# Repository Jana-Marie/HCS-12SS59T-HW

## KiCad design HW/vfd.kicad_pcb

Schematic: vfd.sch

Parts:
BT1: Battery_Cell; BatteryHolder_Keystone_1042_1x18650
C1, C3, C9, C10, C12, C14, C17, C18, C19, C21: 1u; C_0805_2012Metric
C2, C4, C6, C8, C11, C13, C15, C16, C20, C22: 100n; C_0603_1608Metric
C5: 82p; C_0603_1608Metric
C7: TBD; C_0603_1608Metric
D1, D2: D_Schottky; D_SMA
D3: led; LED_0603_1608Metric
L1, L2, L3: 15u; L_Taiyo-Yuden_MD-4040
Q1, Q3, Q5, Q6: 2N7002; SOT-23
Q2, Q4: Si2319CDS; SOT-23
R1: 470; R_0603_1608Metric
R2: 8k2; R_0603_1608Metric
R3, R4, R5, R6, R7, R10: 47; R_0603_1608Metric
R8, R9, R18: 10k; R_0603_1608Metric
R11: TBD; R_0603_1608Metric
R12: 25k; R_0603_1608Metric
R13, R14, R16: 1k; R_0603_1608Metric
R15: 3k; R_0603_1608Metric
R17: 1k5; R_0603_1608Metric
SW1: SW_DIP_x01
T1: Transformer_1P_1S; SRF0703
U1: HCS-12SS59T
U2, U3: MCP1663; SOT-23-5
U4: LM3670MF; SOT-23-5
U5: TP4056; SO-8_5.3x6.2mm_P1.27mm
U6: ESP32-wroom-32; ESP-wroom-32

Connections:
+3V3: C15.1, C17.1, C21.1, C22.1, L3.2, Q2.2 (S), Q4.2 (S), R18.1, U4.4 (FB), U6.2
+5V: C2.1, C16.1, C18.1, D2.1, R2.1, R8.1, R9.1, U1.5
+36V: C3.1, C8.1, C9.1, D1.1, R1.2
CLK: U1.11
CS: U1.10
DIN: U1.12
EN: C20.1, R18.2, U6.3
F+: T1.4, U1.44, U1.45
F-: T1.3, U1.1, U1.2
GND: BT1.2, C1.2, C2.2, C3.2, C4.2, C5.2, C6.2, C7.2, C8.2, C9.2, C10.2, C11.2, C12.2, C13.2, C14.2, C15.2, C16.2, C17.2, C18.2, C19.2, C20.2, C21.2, C22.2, Q1.2 (S), Q3.2 (S), Q5.2 (S), Q6.2 (S), R13.1, R16.1, R17.2, U1.7, U2.2, U3.2, U4.2 (GND), U5.1, U5.3, U6.1, U6.15, U6.38
GPIO15: R7.2
GPIO16: R10.1
unnamed: C4.1, R1.1, U1.6
unnamed: C5.1, R2.2, U1.8
unnamed: C7.1, R11.1, U2.4
unnamed: D1.2, L1.2, R12.2, U2.1
unnamed: D2.2, L2.2, R15.2, U3.1
unnamed: D3.1, R14.1
unnamed: L3.1, U4.5 (SW)
unnamed: Q1.1 (G), R7.1
unnamed: Q1.3 (D), R3.2, R4.2, R8.2
unnamed: Q2.1 (G), R3.1
unnamed: Q2.3 (D), Q3.3 (D), T1.2
unnamed: Q3.1 (G), R4.1
unnamed: Q4.1 (G), R5.2
unnamed: Q4.3 (D), Q5.3 (D), T1.1
unnamed: Q5.1 (G), R6.2
unnamed: Q6.1 (G), R10.2
unnamed: Q6.3 (D), R5.1, R6.1, R9.2
unnamed: R12.1, R13.2, U2.3
unnamed: R14.2, U5.7
unnamed: R15.1, R16.2, U3.3
unnamed: R17.1, U5.2
RST: U1.9
VBAT: BT1.1, C19.1, U5.5
VBAT_SW: C1.1, C6.1, C10.1, C11.1, C12.1, C13.1, L1.1, L2.1, R11.2, U2.5, U3.4, U3.5, U4.1 (Vin), U4.3 (EN)
VUSB: C14.1, D3.2, U5.4, U5.8

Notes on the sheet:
Todo: ESP Unterspannungsschutz USB-seriell Otter

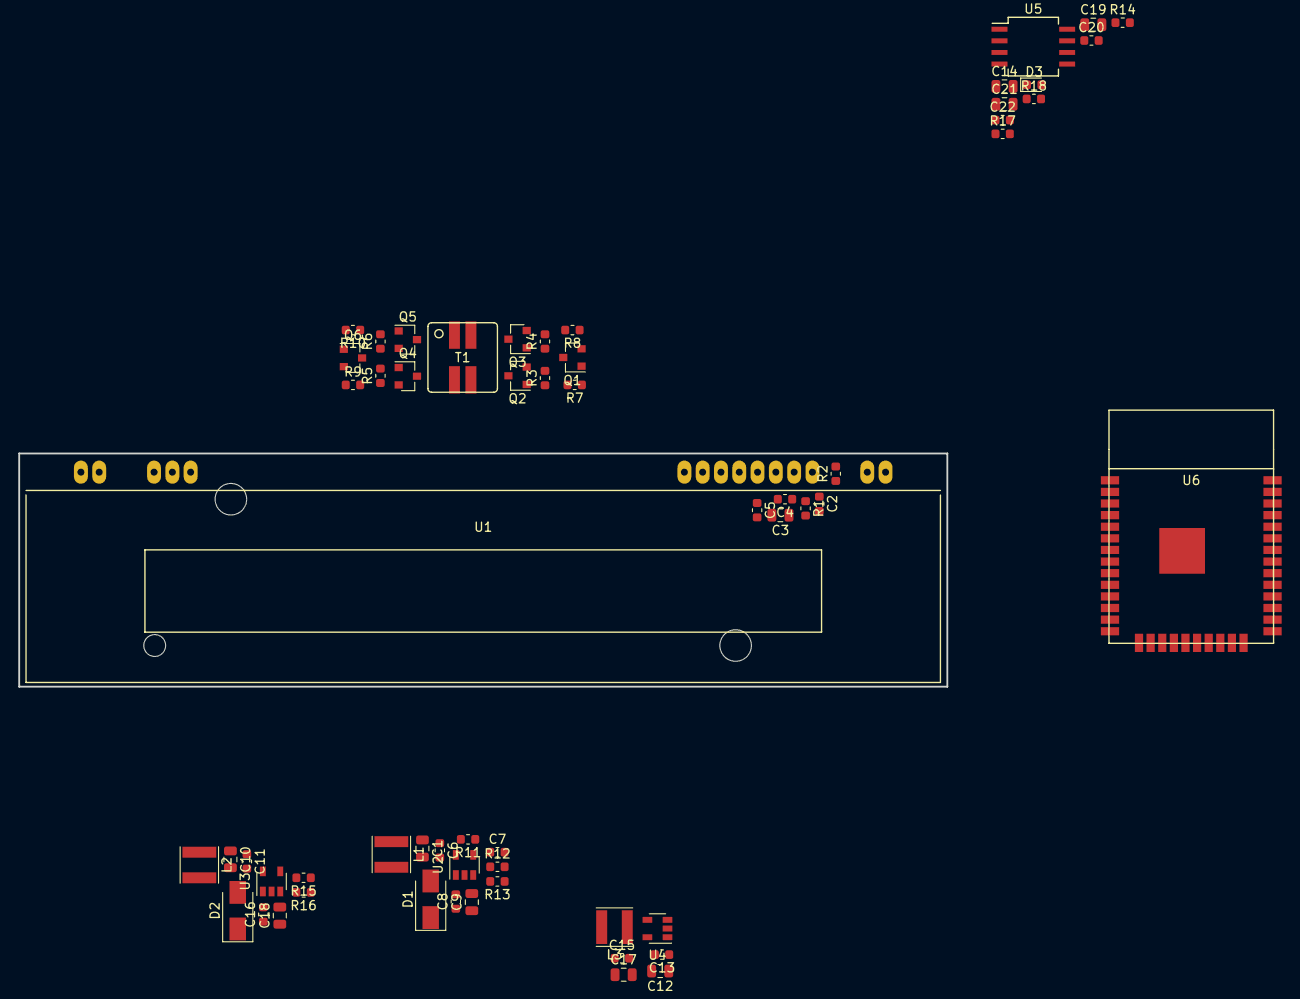
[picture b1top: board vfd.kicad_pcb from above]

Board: 2 copper layers, 101.5 x 25.5 mm, 60 parts (1 on the bottom side), 31 nets, no tracks yet.

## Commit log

2018-09-24 added kicad project
2018-09-24 added heater schmeatic
2018-09-25 added stepups, setdown, battery
2018-09-25 added esp and battery foo
2018-09-26 added gitignore
